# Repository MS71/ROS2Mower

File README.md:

# ROS2Mower
autonomous ROS2 lawn mower

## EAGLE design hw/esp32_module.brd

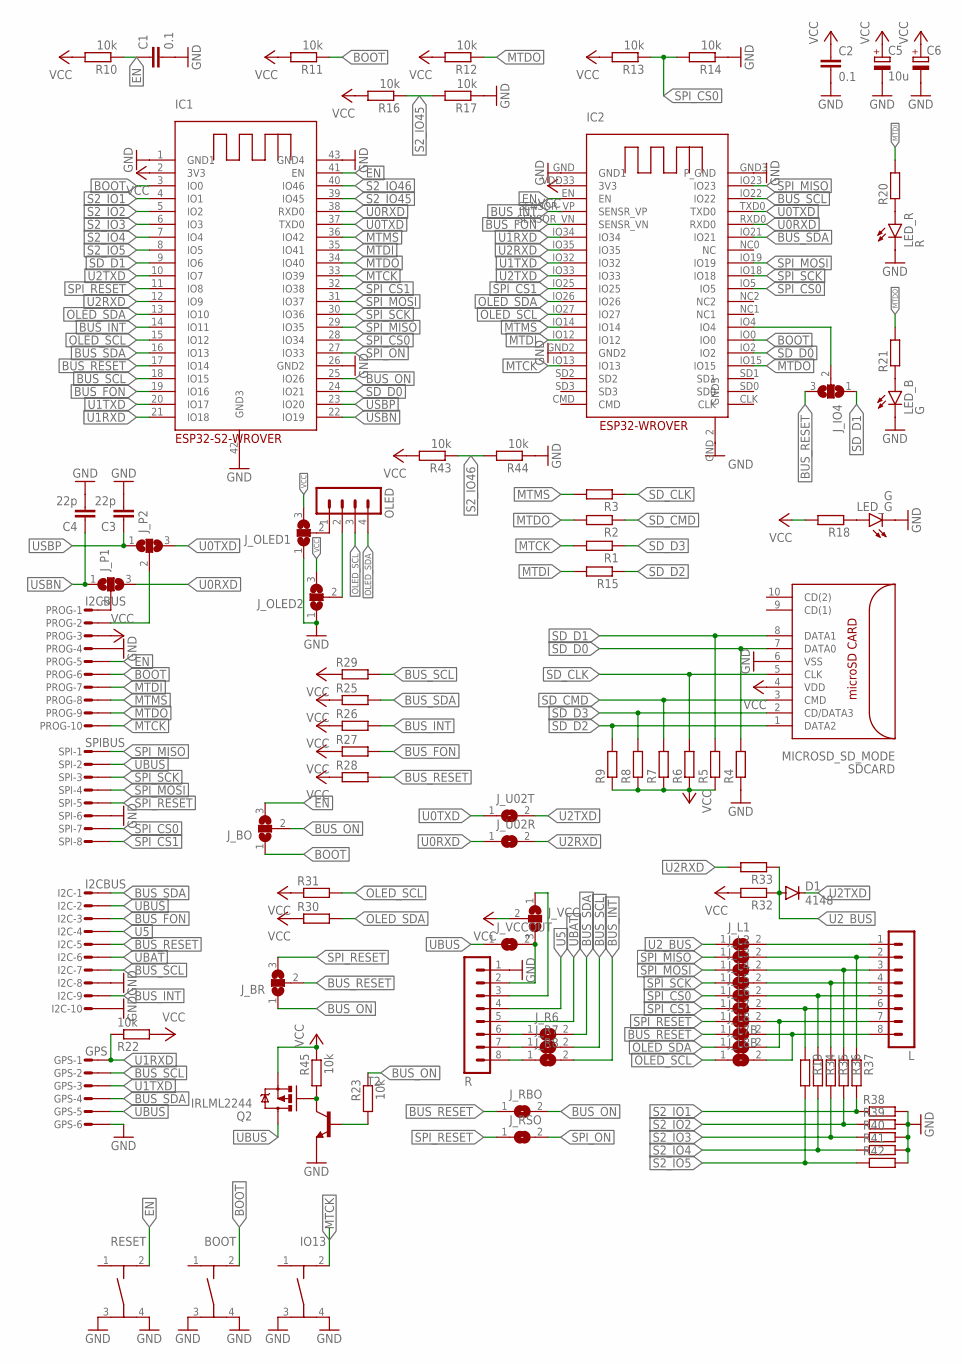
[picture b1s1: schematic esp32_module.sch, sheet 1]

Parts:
BOOT: TASTER-9314_SMD
C1, C2: 0.1; C0805
C3, C4: 22p; C0805
C5: 10u; B/3528-21W
C6: CPOL-EUC/6032-28R; C/6032-28R
D1: 4148; MINIMELF
GPS: GPS; MICROMATCH-6SMD
I2C: I2CBUS; MICROMATCH-10SMD
IC1: ESP32-S2_WROVER; ESP32-S2-WROVER
IC2: ESP32-WROVER
IO13: TASTER-9314_SMD
J_BO: SJ2W; SJ_2
J_BR: SJ2W; SJ_2
J_IO4: SJ2W; SJ_2
J_L1, J_L2, J_L3, J_L4, J_L5, J_L6, J_L7, J_L7B, J_L8, J_L8B: SJ
J_OLED1, J_OLED2: SJ2W; SJ_2
J_P1, J_P2: SJ2W; SJ_2
J_R6, J_R7, J_R8: SJ
J_RBO: SJ
J_RSO: SJ
J_U02R, J_U02T: SJ
J_VCC: SJ2W; SJ_2
J_VCCOUT: SJ
L: MA08-1
LED_B: G; CHIPLED_0805
LED_G: G; CHIPLED_0805
LED_R: R; CHIPLED_0805
OLED: MA04-1
PROG: I2CBUS; MICROMATCH-10SMD
Q2: IRLML2244; SOT23-3
R: MA08-1
R1, R2, R3, R4, R5, R6, R7, R8, R9, R15, R19, R25, R26, R27, R28, R29, R30, R31, R32, R33, R34, R35, R36, R37, R38, R39, R40, R41, R42: R-EU_R0805; R0805
R10, R11, R12, R13, R14, R16, R17, R22, R23, R43, R44, R45: 10k; R0805
R18, R20, R21: R-EU_R0603; R0603
RESET: TASTER-9314_SMD
SDCARD: MICROSD_SD_MODE; MICRO_SD_CONNECTOR
SPI: SPIBUS; MICROMATCH-8-SMD
T2: BC817-16-NPN-SOT23-BEC; SOT23-BEC

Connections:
BOOT: BOOT.2, IC1.3 (IO0), IC2.IO0, J_BO.1, PROG.6, R11.1
BUS_FON: I2C.3, IC1.19 (IO16), IC2.SENSOR_VN (SENSR_VN), R27.2
BUS_INT: I2C.9, IC1.14 (IO11), IC2.SENSOR_VP (SENSR_VP), J_R8.2, R26.2
BUS_ON: IC1.25 (IO26), J_BO.2, J_BR.1, J_RBO.2, R23.1
BUS_RESET: I2C.5, IC1.17 (IO14), J_BR.2, J_IO4.3, J_L8.1, J_RBO.1, R28.2
BUS_SCL: GPS.2, I2C.7, IC1.18 (IO15), IC2.IO22, J_R7.2, R29.2
BUS_SDA: GPS.4, I2C.1, IC1.16 (IO13), IC2.IO21, J_R6.2, R25.2
EN: C1.1, IC1.41 (EN), IC2.EN, J_BO.3, PROG.5, R10.1, RESET.2
GND: BOOT.3, BOOT.4, C1.2, C2.2, C3.2, C4.2, C5.-, C6.-, GPS.6, I2C.8, I2C.10, IC1.1 (GND1), IC1.26 (GND2), IC1.42 (GND3), IC1.43 (GND4), IC2.GND (GND1), IC2.GND2, IC2.GND3 (P_GND), IC2.GND_2 (GND3), IO13.3, IO13.4, J_OLED1.1, J_OLED2.1, LED_B.C, LED_G.C, LED_R.C, PROG.4, R.1, R4.1, R14.1, R17.1, R38.2, R39.2, R40.2, R41.2, R42.2, R44.1, RESET.3, RESET.4, SDCARD.6 (VSS), SPI.6, T2.E
LCD_1: J_OLED1.2, OLED.1
LCD_2: J_OLED2.2, OLED.2
MTCK: IC1.33 (IO39), IC2.IO13, IO13.2, PROG.10, R1.2
MTDI: IC1.35 (IO41), IC2.IO12, PROG.7, R15.2, R20.2
MTDO: IC1.34 (IO40), IC2.IO15, PROG.9, R2.2, R12.1, R21.2
MTMS: IC1.36 (IO42), IC2.IO14, PROG.8, R3.2
unnamed: IC2.IO4, J_IO4.2
unnamed: Q2.1 (G), R45.2, T2.C
unnamed: J_R6.1, R.6
unnamed: LED_G.A, R18.1
unnamed: J_R7.1, R.7
unnamed: J_P1.2, PROG.1
unnamed: J_R8.1, R.8
unnamed: R23.2, T2.B
unnamed: LED_R.A, R20.1
unnamed: LED_B.A, R21.1
unnamed: J_L7.2, J_L7B.2, L.7
unnamed: J_L6.2, L.6, R19.1
unnamed: J_L8.2, J_L8B.2, L.8
unnamed: J_L5.2, L.5, R34.1
unnamed: J_L4.2, L.4, R35.1
unnamed: J_L2.2, L.2, R37.1
unnamed: J_L3.2, L.3, R36.1
unnamed: J_L1.2, L.1
unnamed: J_P2.2, PROG.2
OLED_SCL: IC1.15 (IO12), IC2.IO27, J_L8B.1, OLED.3, R31.2
OLED_SDA: IC1.13 (IO10), IC2.IO26, J_L7B.1, OLED.4, R30.2
S2_IO1: IC1.4 (IO1), R37.2, R38.1
S2_IO2: IC1.5 (IO2), R36.2, R39.1
S2_IO3: IC1.6 (IO3), R35.2, R40.1
S2_IO4: IC1.7 (IO4), R34.2, R41.1
S2_IO5: IC1.8 (IO5), R19.2, R42.1
S2_IO45: IC1.39 (IO45), R16.1, R17.2
S2_IO46: IC1.40 (IO46), R43.1, R44.2
SD_CLK: R3.1, R6.2, SDCARD.5 (CLK)
SD_CMD: R2.1, R7.2, SDCARD.3 (CMD)
SD_D0: IC1.24 (IO21), IC2.IO2, R4.2, SDCARD.7 (DATA0)
SD_D1: IC1.9 (IO6), J_IO4.1, R5.2, SDCARD.8 (DATA1)
SD_D2: R9.2, R15.1, SDCARD.1 (DATA2)
SD_D3: R1.1, R8.2, SDCARD.2 (CD/DATA3)
SPI_CS0: IC1.28 (IO34), IC2.IO5, J_L5.1, R13.1, R14.2, SPI.7
SPI_CS1: IC1.32 (IO38), IC2.IO25, J_L6.1, SPI.8
SPI_MISO: IC1.29 (IO35), IC2.IO23, J_L2.1, SPI.1
SPI_MOSI: IC1.31 (IO37), IC2.IO19, J_L3.1, SPI.4
SPI_ON: IC1.27 (IO33), J_RSO.2
SPI_RESET: IC1.11 (IO8), J_BR.3, J_L7.1, J_RSO.1, SPI.5
SPI_SCK: IC1.30 (IO36), IC2.IO18, J_L4.1, SPI.3
U0RXD: IC1.38 (RXD0), IC2.RXD0, J_P1.3, J_U02R.1
U0TXD: IC1.37 (TXD0), IC2.TXD0, J_P2.3, J_U02T.1
U1RXD: GPS.1, IC1.21 (IO18), IC2.IO34, R22.1
U1TXD: GPS.3, IC1.20 (IO17), IC2.IO32
U2RXD: IC1.12 (IO9), IC2.IO35, J_U02R.2, R33.2
U2TXD: D1.C, IC1.10 (IO7), IC2.IO33, J_U02T.2
U2_BUS: D1.A, J_L1.1, R32.1, R33.1
U5: I2C.4, R.4
U33A: J_VCC.3, J_VCCOUT.2, R.2
U33B: J_VCC.1, R.3
UBAT: I2C.6, R.5
UBUS: GPS.5, I2C.2, J_VCCOUT.1, Q2.3 (D), SPI.2
USBN: C4.1, IC1.22 (IO19), J_P1.1
USBP: C3.1, IC1.23 (IO20), J_P2.1
VCC: C2.1, C5.+, C6.+, IC1.2 (3V3), IC2.VDD33 (3V3), J_OLED1.3, J_OLED2.3, J_VCC.2, PROG.3, Q2.2 (S), R5.1, R6.1, R7.1, R8.1, R9.1, R10.2, R11.2, R12.2, R13.2, R16.2, R18.2, R22.2, R25.1, R26.1, R27.1, R28.1, R29.1, R30.1, R31.1, R32.2, R43.2, R45.1, SDCARD.4 (VDD)

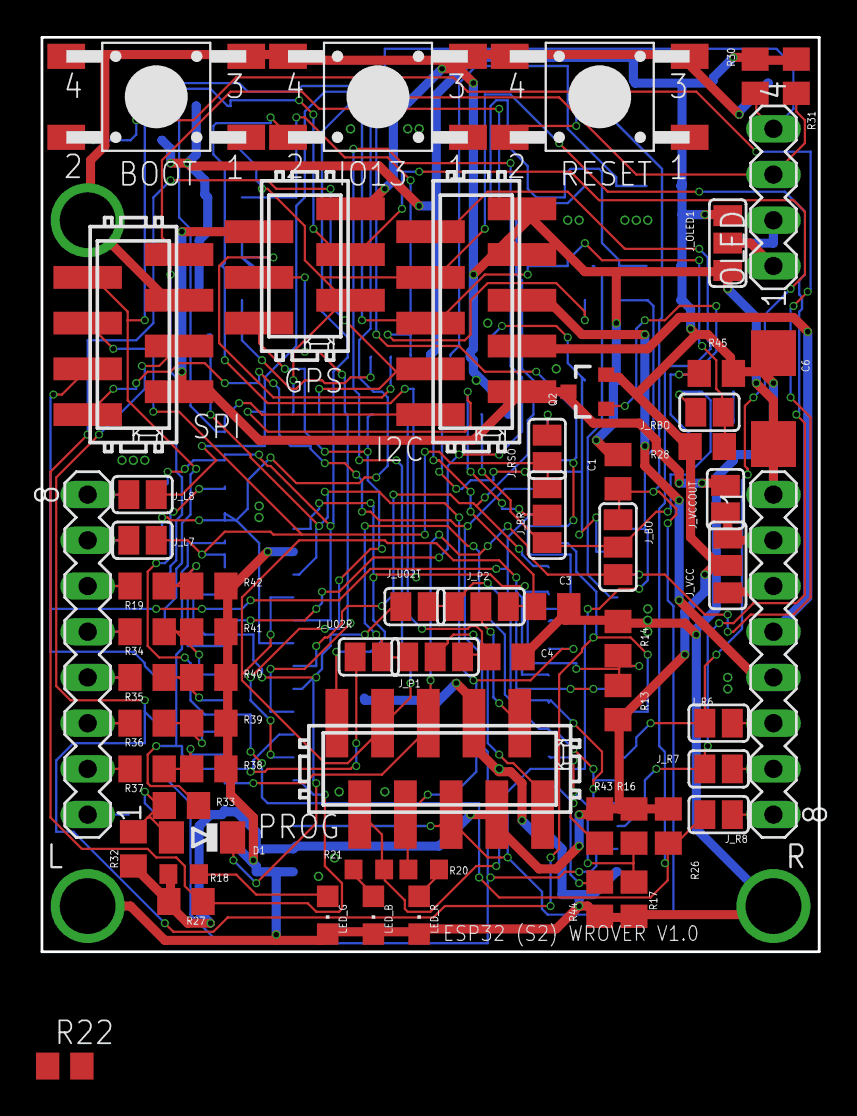
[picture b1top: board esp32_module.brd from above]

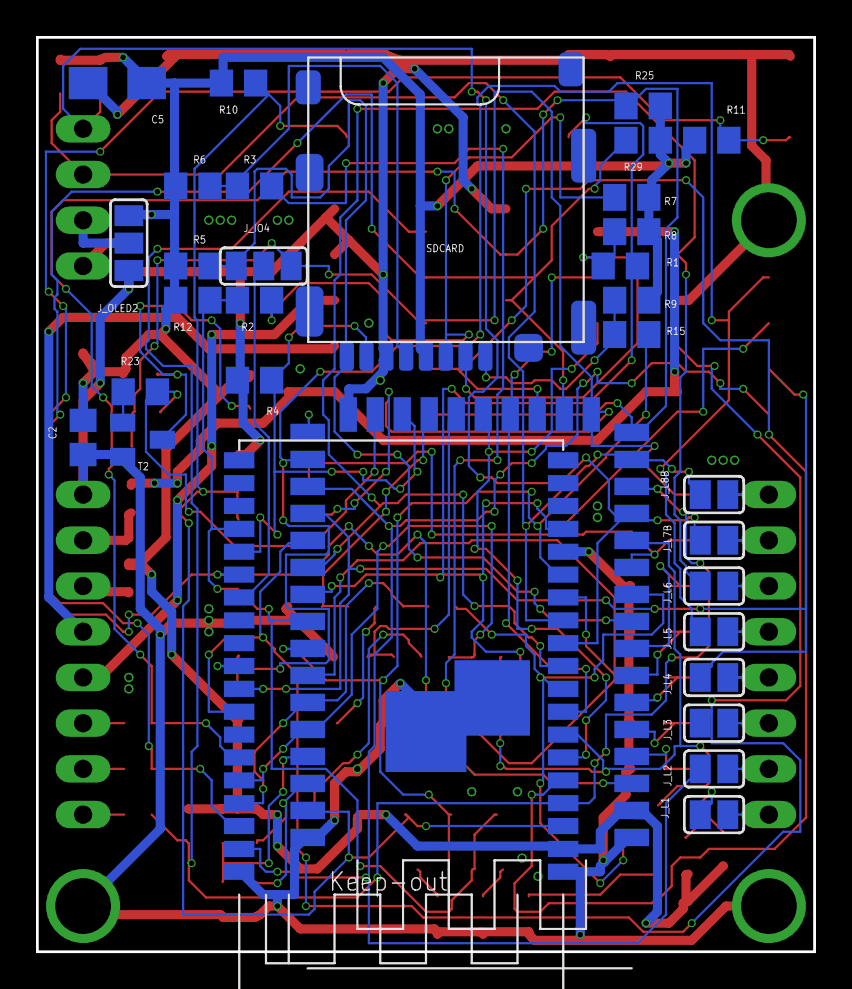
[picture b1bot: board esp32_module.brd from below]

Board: 2 copper layers, 43.2 x 50.8 mm, 95 parts (32 on the bottom side), 71 nets.

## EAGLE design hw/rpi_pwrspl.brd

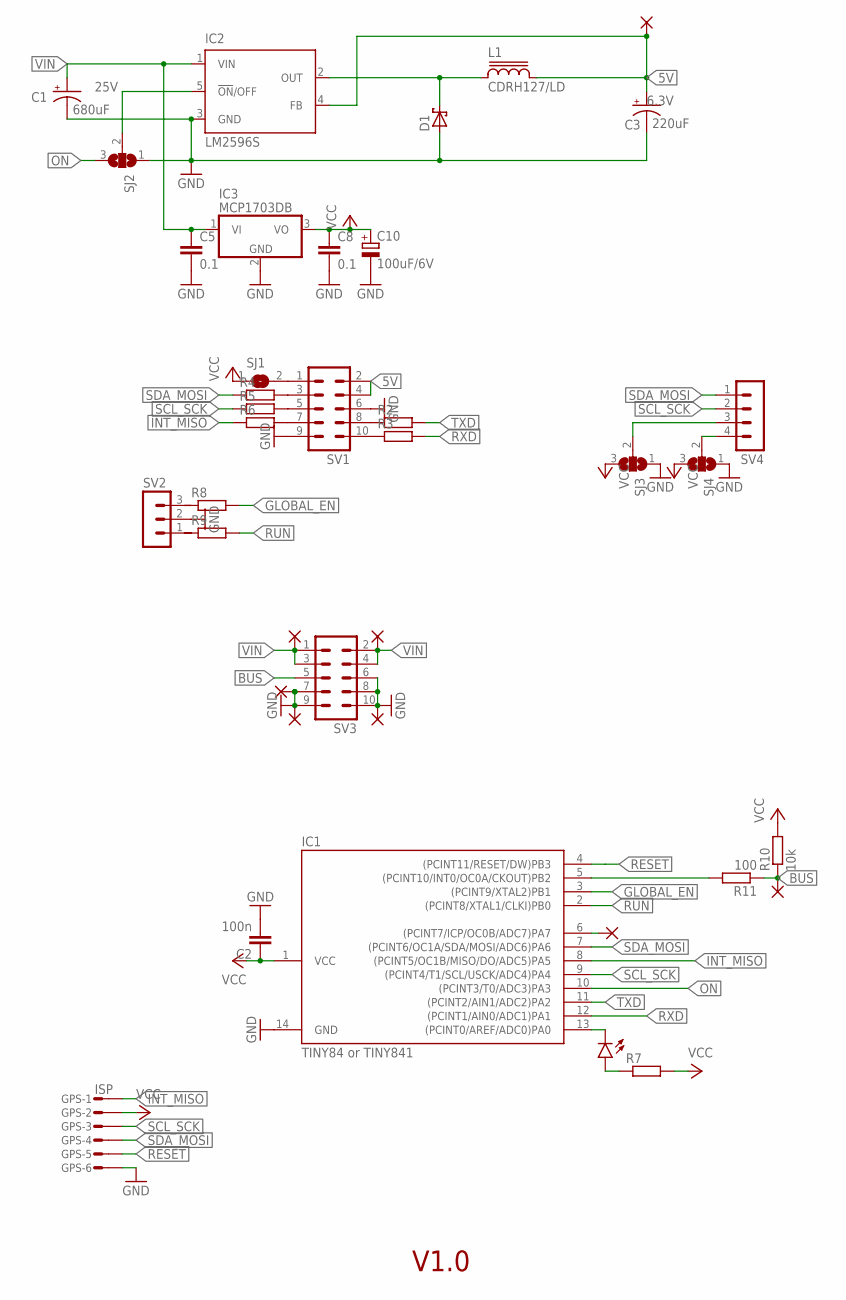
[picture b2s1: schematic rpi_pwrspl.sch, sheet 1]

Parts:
C1: 680uF; E5-10,5; VOLTAGE 25V
C2: 100n; C0805
C3: 220uF; UD-6,3X5,8_NICHICON; VOLTAGE 6.3V
C5, C8: 0.1; C0805
C10: 100uF/6V; B/3528-21R
D1: SCHOTTKY-DIODESMD; SMB
GPS: ISP; MICROMATCH-6SMD
IC1: TINY84 or TINY841; SOIC14
IC2: LM2596S; TO263-5
IC3: MCP1703DB; SOT223
L1: CDRH127/LD
LED: LEDCHIPLED_0805; CHIPLED_0805
PAD1, PAD2, PAD3, PAD6, PAD7: 1,6/0,9
PAD4, PAD5, PAD8: 2,54/1,1
R2, R3, R4, R5, R6, R8, R9: R-EU_M0805; M0805
R7: 100; R0603
R10: 10k; M0805
R11: 100; M0805
SJ1: SJ
SJ2, SJ3, SJ4: SJ2W; SJ_2
SV1, SV3: MA05-2
SV2: MA03-1
SV4: MA04-1

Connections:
5V: C3.+, IC2.4 (FB), L1.2, PAD6.1, SV1.2, SV1.4
BUS: PAD5.1, R10.1, R11.1, SV3.5
GLOBAL_EN: IC1.3 ((PCINT9/XTAL2)PB1), R8.2
GND: C1.-, C2.2, C3.-, C5.2, C8.2, C10.-, D1.A, GPS.6, IC1.14 (GND), IC2.3 (GND), IC3.2 (GND), PAD2.1, PAD3.1, PAD8.1, SJ2.1, SJ3.1, SJ4.1, SV1.6, SV1.9, SV2.2, SV3.6, SV3.7, SV3.8, SV3.9, SV3.10
INT_MISO: GPS.1, IC1.8 ((PCINT5/OC1B/MISO/DO/ADC5)PA5), R6.1
unnamed: SJ1.2, SV1.1
unnamed: R2.1, SV1.8
unnamed: R3.1, SV1.10
unnamed: R4.2, SV1.3
unnamed: LED.A, R7.1
unnamed: R5.2, SV1.5
unnamed: R6.2, SV1.7
unnamed: IC2.5 (!ON!/OFF), SJ2.2
unnamed: SJ4.2, SV4.4
unnamed: SJ3.2, SV4.3
unnamed: IC1.6 ((PCINT7/ICP/OC0B/ADC7)PA7), PAD7.1
unnamed: IC1.5 ((PCINT10/INT0/OC0A/CKOUT)PB2), R11.2
ON: IC1.10 ((PCINT3/T0/ADC3)PA3), SJ2.3
OUT: D1.C, IC2.2 (OUT), L1.1
PA0: IC1.13 ((PCINT0/AREF/ADC0)PA0), LED.C
RESET: GPS.5, IC1.4 ((PCINT11/RESET/DW)PB3)
RUN: IC1.2 ((PCINT8/XTAL1/CLKI)PB0), R9.2
RXD: IC1.12 ((PCINT1/AIN0/ADC1)PA1), R3.2
SCL_SCK: GPS.3, IC1.9 ((PCINT4/T1/SCL/USCK/ADC4)PA4), R5.1, SV4.2
SDA_MOSI: GPS.4, IC1.7 ((PCINT6/OC1A/SDA/MOSI/ADC6)PA6), R4.1, SV4.1
TXD: IC1.11 ((PCINT2/AIN1/ADC2)PA2), R2.2
VCC: C2.1, C8.1, C10.+, GPS.2, IC1.1 (VCC), IC3.3 (VO), R7.2, R10.2, SJ1.1, SJ3.3, SJ4.3
VIN: C1.+, C5.1, IC2.1 (VIN), IC3.1 (VI), PAD1.1, PAD4.1, SV3.1, SV3.2, SV3.3, SV3.4

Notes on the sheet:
V1.0

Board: 2 copper layers, 39 parts (5 on the bottom side), 28 nets, no tracks yet.

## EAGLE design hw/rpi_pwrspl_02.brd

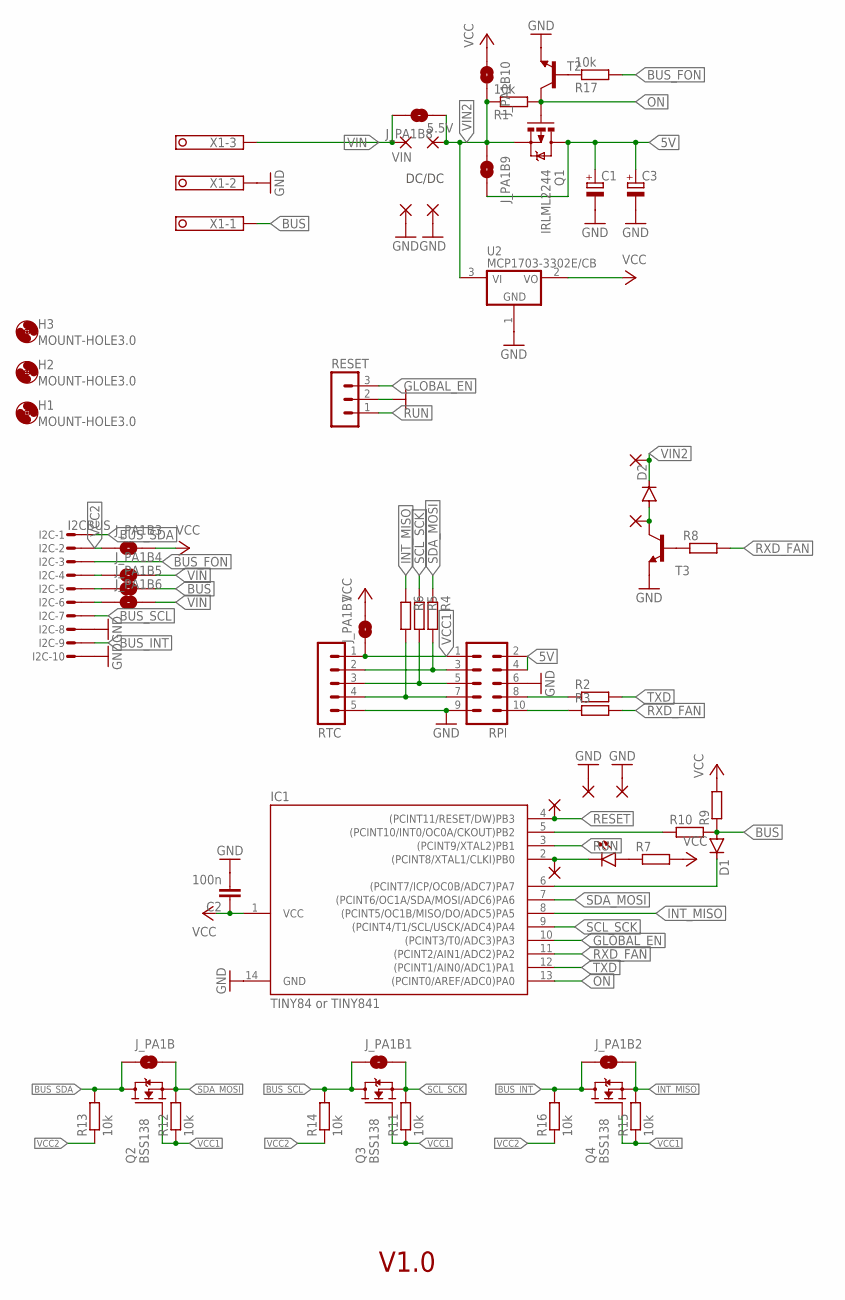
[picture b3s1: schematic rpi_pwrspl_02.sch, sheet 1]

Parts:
5.5V: 2,54/1,0
C1: CPOL-EUE5-5; E5-5
C2: 100n; C0805
C3: CPOL-EU085CS-1AR; 085CS_1AR
D1, D2: DIODE-MINIMELF; MINIMELF
DW, DW1, DW2, DW3, DW4, DW5: 1,6/0,9
H1, H2, H3: MOUNT-HOLE3.0; 3,0
I2C: I2CBUS; MICROMATCH-10SMD
IC1: TINY84 or TINY841; SOIC14
J_PA1B, J_PA1B1, J_PA1B2, J_PA1B3, J_PA1B4, J_PA1B5, J_PA1B6, J_PA1B7, J_PA1B8, J_PA1B9, J_PA1B10: JUMPER-SMT_2_NO_NO-SILK; SMT-JUMPER_2_NO_NO-SILK
LED: LEDCHIPLED_0805; CHIPLED_0805
PAD1, PAD2: 2,54/1,0
Q1: IRLML2244; SOT23-3
Q2, Q3, Q4: BSS138; SOT23
R1, R11, R12, R13, R14, R15, R16, R17: 10k; R0805
R2, R3, R4, R5, R6, R8, R9, R10: R-EU_M0805; M0805
R7: 100; R0603
RESET: MA03-1
RPI: MA05-2
RTC: MA05-1
T2, T3: BC817-16-NPN-SOT23-BEC; SOT23-BEC
U2: MCP1703-3302E/CB; SOT23A_MICROCHIP_CB
VIN: 2,54/1,0
X1: 1751251

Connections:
5V: C1.+, C3.+, J_PA1B9.2, Q1.3 (D), RPI.2, RPI.4
BUS: D1.A, J_PA1B5.2, R9.1, R10.2, X1.1
BUS_FON: I2C.3, R17.2
BUS_INT: I2C.9, J_PA1B2.1, Q4.3 (D), R16.2
BUS_SCL: I2C.7, J_PA1B1.1, Q3.3 (D), R14.2
BUS_SDA: I2C.1, J_PA1B.1, Q2.3 (D), R13.2
GLOBAL_EN: IC1.10 ((PCINT3/T0/ADC3)PA3), RESET.3
GND: C1.-, C2.2, C3.-, DW2.1, DW3.1, I2C.8, I2C.10, IC1.14 (GND), PAD1.1, PAD2.1, RESET.2, RPI.6, RPI.9, RTC.5, T2.E, T3.E, U2.1 (GND), X1.2
INT_MISO: IC1.8 ((PCINT5/OC1B/MISO/DO/ADC5)PA5), J_PA1B2.2, Q4.2 (S), R6.1, R15.2
unnamed: I2C.4, J_PA1B4.1
unnamed: R4.2, RPI.3, RTC.2
unnamed: R2.1, RPI.8
unnamed: R3.1, RPI.10
unnamed: R5.2, RPI.5, RTC.3
unnamed: LED.A, R7.1
unnamed: R6.2, RPI.7, RTC.4
unnamed: D2.A, DW4.1, T3.C
unnamed: IC1.5 ((PCINT10/INT0/OC0A/CKOUT)PB2), R10.1
unnamed: D1.C, IC1.6 ((PCINT7/ICP/OC0B/ADC7)PA7)
unnamed: DW1.1, IC1.2 ((PCINT8/XTAL1/CLKI)PB0), LED.C
unnamed: R8.1, T3.B
unnamed: R17.1, T2.B
unnamed: I2C.6, J_PA1B6.1
unnamed: I2C.5, J_PA1B5.1
ON: IC1.13 ((PCINT0/AREF/ADC0)PA0), Q1.1 (G), R1.2, T2.C
RESET: DW.1, IC1.4 ((PCINT11/RESET/DW)PB3)
RUN: IC1.3 ((PCINT9/XTAL2)PB1), RESET.1
RXD_FAN: IC1.11 ((PCINT2/AIN1/ADC2)PA2), R3.2, R8.2
SCL_SCK: IC1.9 ((PCINT4/T1/SCL/USCK/ADC4)PA4), J_PA1B1.2, Q3.2 (S), R5.1, R11.2
SDA_MOSI: IC1.7 ((PCINT6/OC1A/SDA/MOSI/ADC6)PA6), J_PA1B.2, Q2.2 (S), R4.1, R12.2
TXD: IC1.12 ((PCINT1/AIN0/ADC1)PA1), R2.2
VCC: C2.1, IC1.1 (VCC), J_PA1B3.2, J_PA1B7.2, J_PA1B10.1, R7.2, R9.2, U2.2 (VO)
VCC1: J_PA1B7.1, Q2.1 (G), Q3.1 (G), Q4.1 (G), R11.1, R12.1, R15.1, RPI.1, RTC.1
VCC2: I2C.2, J_PA1B3.1, R13.1, R14.1, R16.1
VIN: J_PA1B4.2, J_PA1B6.2, J_PA1B8.2, VIN.1, X1.3
VIN2: 5.5V.1, D2.C, DW5.1, J_PA1B8.1, J_PA1B9.1, J_PA1B10.2, Q1.2 (S), R1.1, U2.3 (VI)

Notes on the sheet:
V1.0
DC/DC

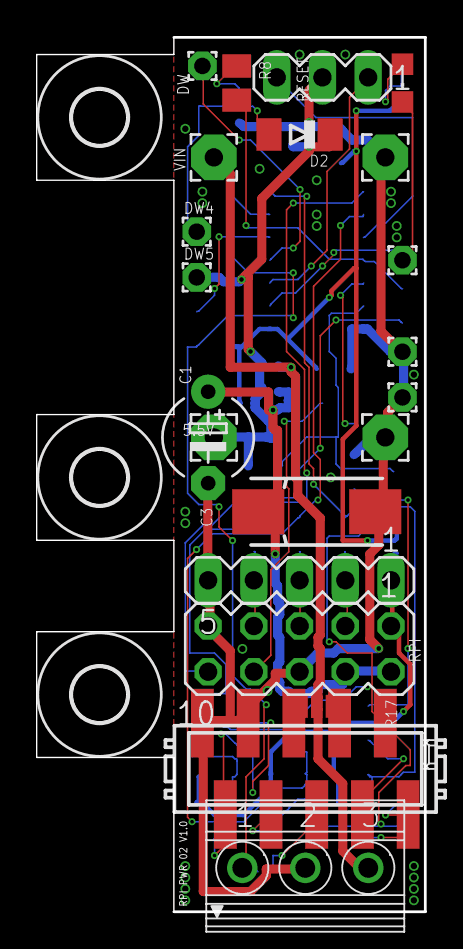
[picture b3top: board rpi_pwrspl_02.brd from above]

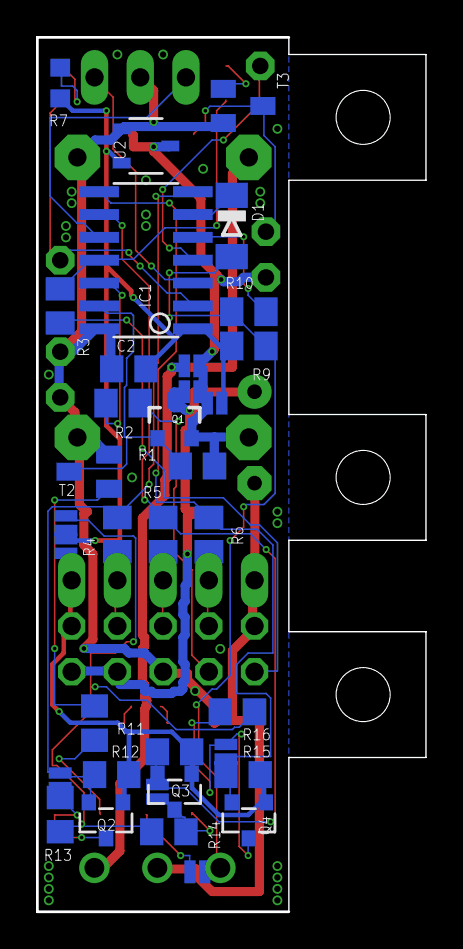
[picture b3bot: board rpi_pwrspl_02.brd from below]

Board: 2 copper layers, 21.6 x 48.6 mm, 60 parts (35 on the bottom side), 36 nets.

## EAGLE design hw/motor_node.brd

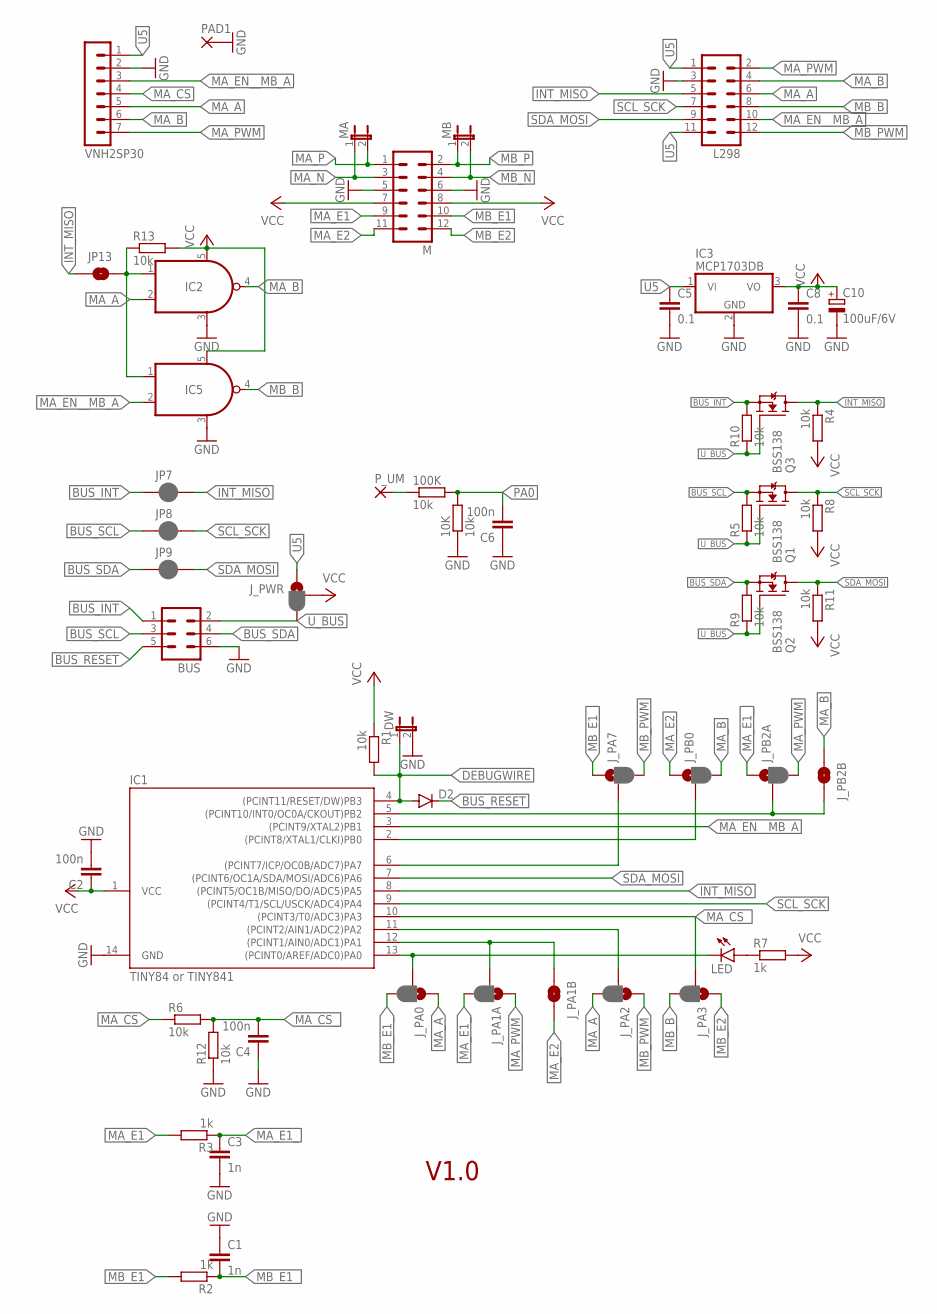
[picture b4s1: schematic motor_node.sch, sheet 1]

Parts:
10K, 100K: 10k; M0805
BUS: ML6
C1, C3: 1n; C0805
C2, C4, C6: 100n; C0805
C5, C8: 0.1; C0805
C10: 100uF/6V; B/3528-21R
D2: DIODE-MINIMELF; MINIMELF
DW: JP1E; JP1
IC1: TINY84 or TINY841; SOIC14
IC2, IC5: AHC00-DB; SOT-23/5
IC3: MCP1703DB; SOT223
JP7, JP8, JP9: JUMPER-SMT_2_NC_PASTE_NO-SILK; SMT-JUMPER_2_NC_PASTE_NO-SILK
JP13: JUMPER-SMT_2_NO_NO-SILK; SMT-JUMPER_2_NO_NO-SILK
J_PA0, J_PA1A, J_PA2, J_PA3, J_PA7: JUMPER-SMT_3_1-NC_PASTE_NO-SILK; SMT-JUMPER_3_1-NC_PASTE_NO-SILK
J_PA1B: JUMPER-SMT_2_NO_NO-SILK; SMT-JUMPER_2_NO_NO-SILK
J_PB0, J_PB2A: JUMPER-SMT_3_1-NC_PASTE_NO-SILK; SMT-JUMPER_3_1-NC_PASTE_NO-SILK
J_PB2B: JUMPER-SMT_2_NO_NO-SILK; SMT-JUMPER_2_NO_NO-SILK
J_PWR: JUMPER-SMT_3_1-NC_PASTE_NO-SILK; SMT-JUMPER_3_1-NC_PASTE_NO-SILK
L298: MA06-2
LED: LEDCHIPLED_0805; CHIPLED_0805
M: MA06-2
MA: JP1E; JP1
MB: JP1E; JP1
PAD1: 2,54/0,8
P_UM: 1,6/0,8
Q1, Q2, Q3: BSS138; SOT23
R1, R4, R6, R8, R11, R12: 10k; M0805
R2, R3: 1k; M0805
R5, R9, R10, R13: 10k; R0805
R7: 1k; R0603
VNH2SP30: MA07-1

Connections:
BUS_INT: BUS.1, JP7.1, Q3.2 (S), R10.2
BUS_RESET: BUS.5, D2.C
BUS_SCL: BUS.3, JP8.1, Q1.2 (S), R5.2
BUS_SDA: BUS.4, JP9.1, Q2.2 (S), R9.2
DEBUGWIRE: D2.A, DW.1, IC1.4 ((PCINT11/RESET/DW)PB3), R1.2
GND: 10K.1, BUS.6, C1.1, C2.2, C3.2, C4.1, C5.2, C6.1, C8.2, C10.-, DW.2, IC1.14 (GND), IC2.3 (GND), IC3.2 (GND), IC5.3 (GND), L298.3, M.5, M.6, PAD1.1, R12.1, VNH2SP30.2
INT_MISO: IC1.8 ((PCINT5/OC1B/MISO/DO/ADC5)PA5), JP7.2, JP13.1, L298.5, Q3.3 (D), R4.1
MA_A: IC2.2 (I1), J_PA0.1, J_PA2.3, L298.6, VNH2SP30.5
MA_B: IC2.4 (O), J_PB0.3, J_PB2B.1, L298.4, VNH2SP30.6
MA_CS: R6.1, VNH2SP30.4
MA_CS_: C4.2, IC1.10 ((PCINT3/T0/ADC3)PA3), J_PA3.2, R6.2, R12.2
MA_E1: M.9, R3.2
MA_E1_: C3.1, J_PA1A.3, J_PB2A.1, R3.1
MA_E2: J_PA1B.2, J_PB0.1, M.11
MA_EN__MB_A: IC1.3 ((PCINT9/XTAL2)PB1), IC5.2 (I1), L298.10, VNH2SP30.3
MA_N: M.3, MA.1
MA_P: M.1, MA.2
MA_PWM: J_PA1A.1, J_PB2A.3, L298.2, VNH2SP30.7
MB_B: IC5.4 (O), J_PA3.3, L298.8
MB_E1: M.10, R2.2
MB_E1_: C1.2, J_PA0.3, J_PA7.1, R2.1
MB_E2: J_PA3.1, M.12
MB_N: M.4, MB.2
MB_P: M.2, MB.1
MB_PWM: J_PA2.1, J_PA7.3, L298.12
unnamed: 100K.1, P_UM.1
unnamed: IC2.1 (I0), IC5.1 (I0), JP13.2, R13.1
unnamed: LED.A, R7.1
PA0: 10K.2, 100K.2, C6.2, IC1.13 ((PCINT0/AREF/ADC0)PA0), J_PA0.2, LED.C
PA1: IC1.12 ((PCINT1/AIN0/ADC1)PA1), J_PA1A.2, J_PA1B.1
PA2: IC1.11 ((PCINT2/AIN1/ADC2)PA2), J_PA2.2
PA7: IC1.6 ((PCINT7/ICP/OC0B/ADC7)PA7), J_PA7.2
PB0: IC1.2 ((PCINT8/XTAL1/CLKI)PB0), J_PB0.2
PB2: IC1.5 ((PCINT10/INT0/OC0A/CKOUT)PB2), J_PB2A.2, J_PB2B.2
SCL_SCK: IC1.9 ((PCINT4/T1/SCL/USCK/ADC4)PA4), JP8.2, L298.7, Q1.3 (D), R8.1
SDA_MOSI: IC1.7 ((PCINT6/OC1A/SDA/MOSI/ADC6)PA6), JP9.2, L298.9, Q2.3 (D), R11.1
U5: C5.1, IC3.1 (VI), J_PWR.1, L298.1, L298.11, VNH2SP30.1
U_BUS: BUS.2, J_PWR.3, Q1.1 (G), Q2.1 (G), Q3.1 (G), R5.1, R9.1, R10.1
VCC: C2.1, C8.1, C10.+, IC1.1 (VCC), IC2.5 (VDD), IC3.3 (VO), IC5.5 (VDD), J_PWR.2, M.7, M.8, R1.1, R4.2, R7.2, R8.2, R11.2, R13.2

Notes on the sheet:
V1.0

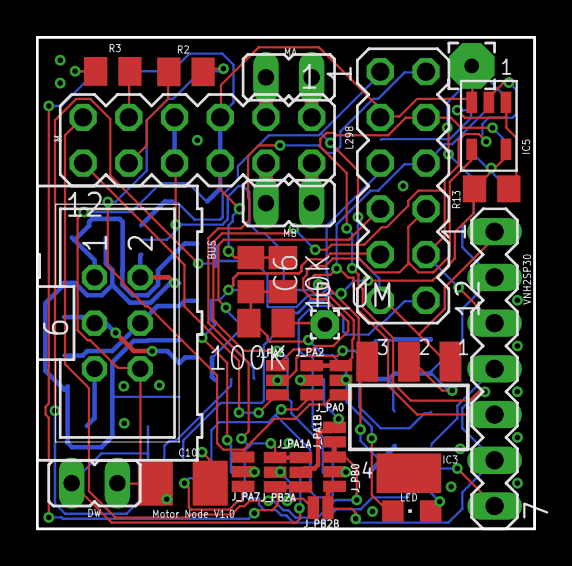
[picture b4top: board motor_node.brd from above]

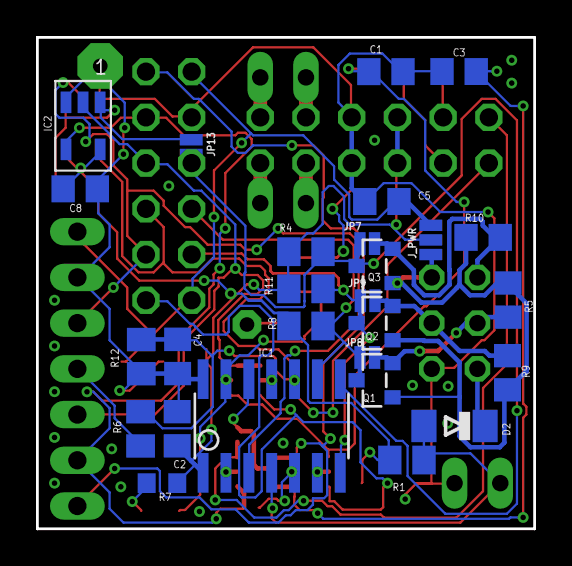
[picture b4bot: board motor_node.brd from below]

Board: 2 copper layers, 27.6 x 27.3 mm, 55 parts (27 on the bottom side), 39 nets.

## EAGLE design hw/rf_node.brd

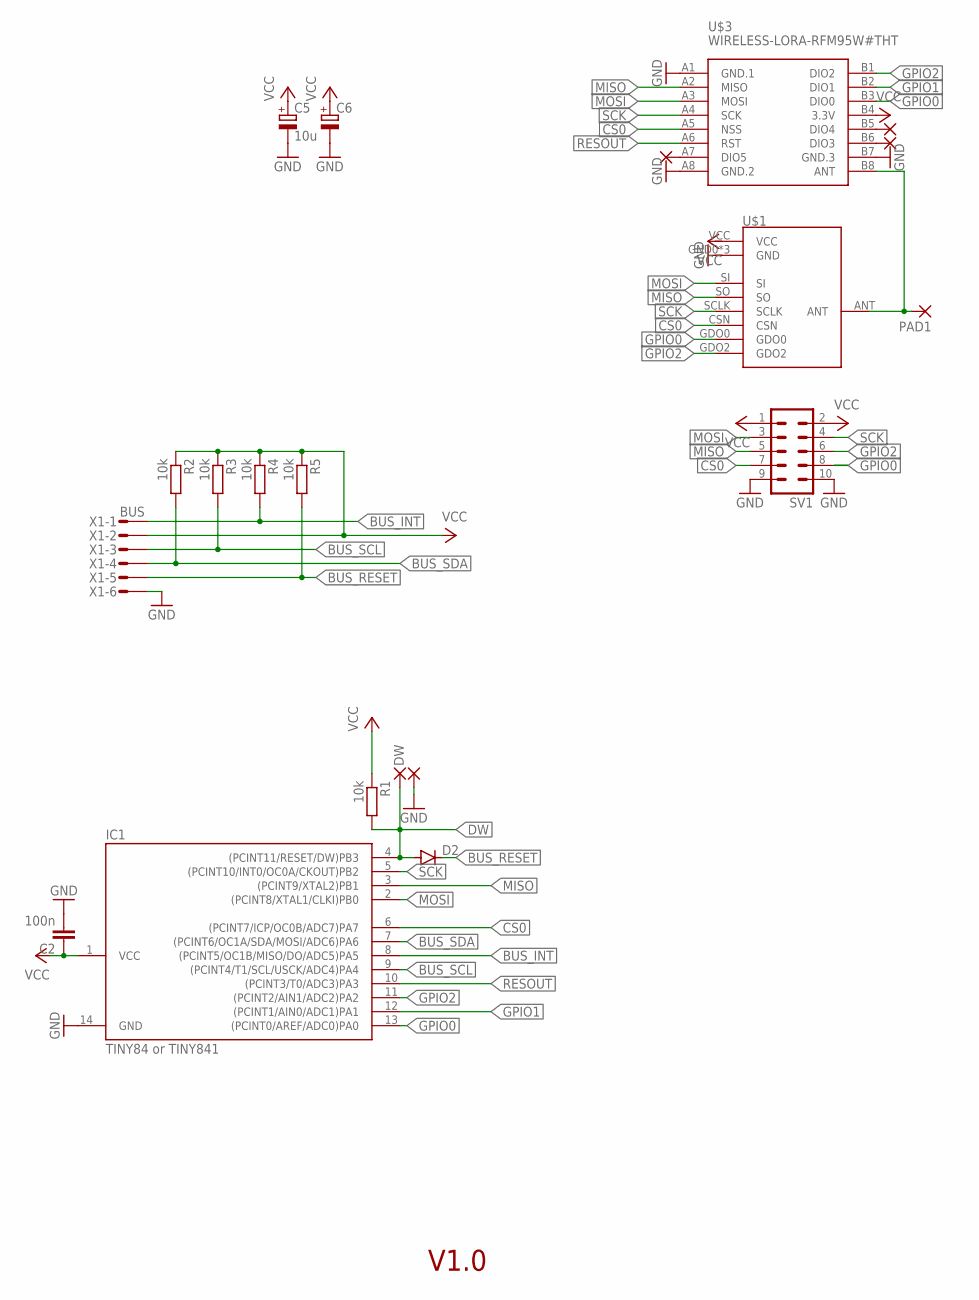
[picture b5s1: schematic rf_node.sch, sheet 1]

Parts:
C2: 100n; C0805
C5: 10u; B/3528-21W
C6: CPOL-EUC/6032-28R; C/6032-28R
D2: DIODE-MINIMELF; MINIMELF
DW: 1,6/0,9
GND_: 1,6/0,9
IC1: TINY84 or TINY841; SOIC14
PAD1, PAD2, PAD3, PAD4: 1,6/0,8
R1, R2, R3, R4, R5: 10k; M0805
SV1: MA05-2
U$1: CC1101
U$3: WIRELESS-LORA-RFM95W#THT
X1: BUS; MICROMATCH-6

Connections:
BUS_INT: IC1.8 ((PCINT5/OC1B/MISO/DO/ADC5)PA5), R4.2, X1.1
BUS_RESET: D2.C, R5.2, X1.5
BUS_SCL: IC1.9 ((PCINT4/T1/SCL/USCK/ADC4)PA4), R3.2, X1.3
BUS_SDA: IC1.7 ((PCINT6/OC1A/SDA/MOSI/ADC6)PA6), R2.2, X1.4
CS0: IC1.6 ((PCINT7/ICP/OC0B/ADC7)PA7), SV1.7, U$1.CSN, U$3.A5 (NSS)
DW: D2.A, DW.1, IC1.4 ((PCINT11/RESET/DW)PB3), R1.2
GND: C2.2, C5.-, C6.-, GND_.1, IC1.14 (GND), SV1.9, SV1.10, U$1.GND0 (GND), U$1.GND1 (GND), U$1.GND2 (GND), U$3.A1 (GND.1), U$3.A8 (GND.2), U$3.B7 (GND.3), X1.6
GPIO0: IC1.13 ((PCINT0/AREF/ADC0)PA0), SV1.8, U$1.GDO0, U$3.B3 (DIO0)
GPIO1: IC1.12 ((PCINT1/AIN0/ADC1)PA1), U$3.B2 (DIO1)
GPIO2: IC1.11 ((PCINT2/AIN1/ADC2)PA2), SV1.6, U$1.GDO2, U$3.B1 (DIO2)
MISO: IC1.3 ((PCINT9/XTAL2)PB1), SV1.5, U$1.SO, U$3.A2 (MISO)
MOSI: IC1.2 ((PCINT8/XTAL1/CLKI)PB0), SV1.3, U$1.SI, U$3.A3 (MOSI)
unnamed: PAD1.1, U$1.ANT, U$3.B8 (ANT)
unnamed: PAD2.1, U$3.B6 (DIO3)
unnamed: PAD3.1, U$3.B5 (DIO4)
unnamed: PAD4.1, U$3.A7 (DIO5)
RESOUT: IC1.10 ((PCINT3/T0/ADC3)PA3), U$3.A6 (RST)
SCK: IC1.5 ((PCINT10/INT0/OC0A/CKOUT)PB2), SV1.4, U$1.SCLK, U$3.A4 (SCK)
VCC: C2.1, C5.+, C6.+, IC1.1 (VCC), R1.1, R2.1, R3.1, R4.1, R5.1, SV1.1, SV1.2, U$1.VCC, U$3.B4 (3.3V), X1.2

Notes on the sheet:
V1.0

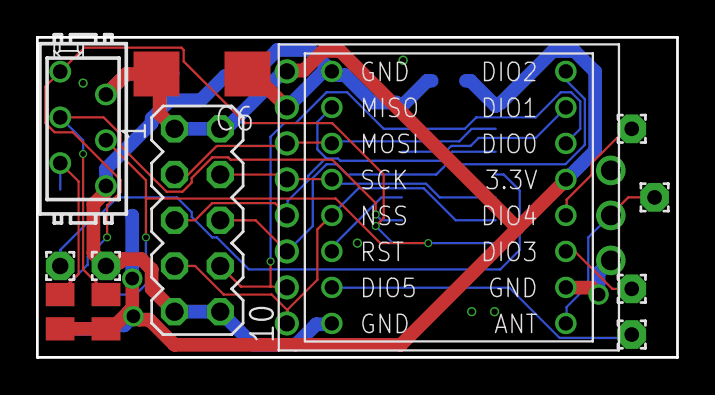
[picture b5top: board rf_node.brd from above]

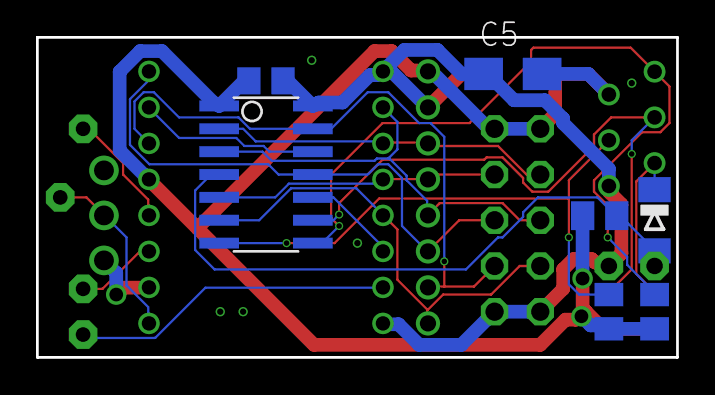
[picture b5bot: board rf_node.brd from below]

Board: 2 copper layers, 35.6 x 17.8 mm, 20 parts (7 on the bottom side), 19 nets.

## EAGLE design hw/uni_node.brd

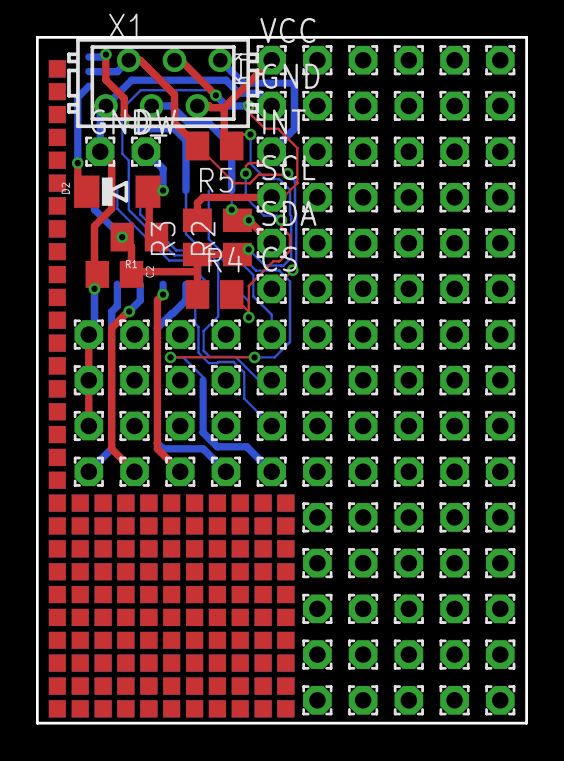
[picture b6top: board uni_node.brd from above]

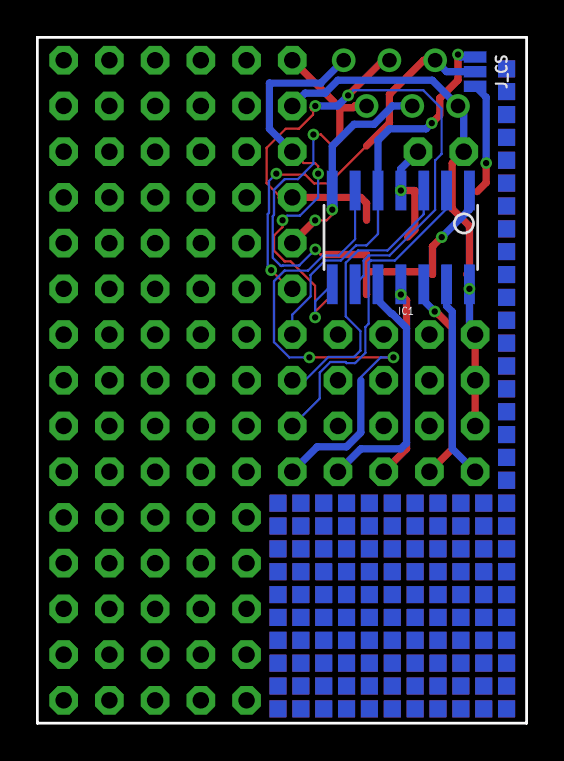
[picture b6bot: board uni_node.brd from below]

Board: 2 copper layers, 27.2 x 38.1 mm, 113 parts (2 on the bottom side), 16 nets.

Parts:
C2: 100n; C0805
CS: 1,6/0,9
D2: MINIMELF
DW: 1,6/0,9
GND: 1,6/0,9
GND_: 1,6/0,9
IC1: TINY84 or TINY841; SOIC14
INT, INT0: 1,6/0,9
J_CS: SMT-JUMPER_3_1-NC_PASTE_NO-SILK
PA0, PA1, PA2, PA3, PA7: 1,6/0,9
PAD1, PAD2, PAD3, PAD4, PAD5, PAD7, PAD8, PAD10, PAD11, PAD12, PAD13, PAD14, PAD15, PAD16, PAD18, PAD19, PAD20, PAD21, PAD22, PAD24, PAD25, PAD26, PAD28, PAD29, PAD30, PAD31, PAD33, PAD34, PAD35, PAD36, PAD37, PAD38, PAD39, PAD40, PAD43, PAD44, PAD45, PAD46, PAD47, PAD48, PAD49, PAD50, PAD51, PAD52, PAD53, PAD54, PAD55, PAD56, PAD57, PAD59, PAD60, PAD61, PAD62, PAD65, PAD66, PAD67, PAD68, PAD69, PAD70, PAD71, PAD72, PAD74, PAD75, PAD76, PAD78, PAD79, PAD80, PAD81, PAD82, PAD83, PAD84, PAD85, PAD86, PAD87, PAD89, PAD90, PAD91, PAD93, PAD94, PAD95, PAD96, PAD97, PAD98, PAD99, PAD100, PAD101, PAD102: 1,6/0,9
PB0, PB1: 1,6/0,9
R1, R2, R3, R4, R5: 10k; M0805
SCL: 1,6/0,9
SDA: 1,6/0,9
VCC: 1,6/0,9
X1: BUS; MICROMATCH-6

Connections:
BUS_INT: IC1.8, INT.1, R4.2, X1.1
BUS_P5: CS.1, J_CS.2, R5.2, X1.5
BUS_RESET: D2.C, J_CS.3
BUS_SCL: IC1.9, R3.2, SCL.1, X1.3
BUS_SDA: IC1.7, R2.2, SDA.1, X1.4
DW: D2.A, DW.1, IC1.4, R1.2
GND: C2.2, GND.1, GND_.1, IC1.14, PAD100.1, PAD101.1, PAD102.1, X1.6
INT0: IC1.5, INT0.1, J_CS.1
PA0: IC1.13, PA0.1
PA1: IC1.12, PA1.1
PA2: IC1.11, PA2.1
PA3: IC1.10, PA3.1
PA7: IC1.6, PA7.1
PB0: IC1.2, PB0.1
PB1: IC1.3, PB1.1
VCC: C2.1, IC1.1, R1.1, R2.1, R3.1, R4.1, R5.1, VCC.1, X1.2

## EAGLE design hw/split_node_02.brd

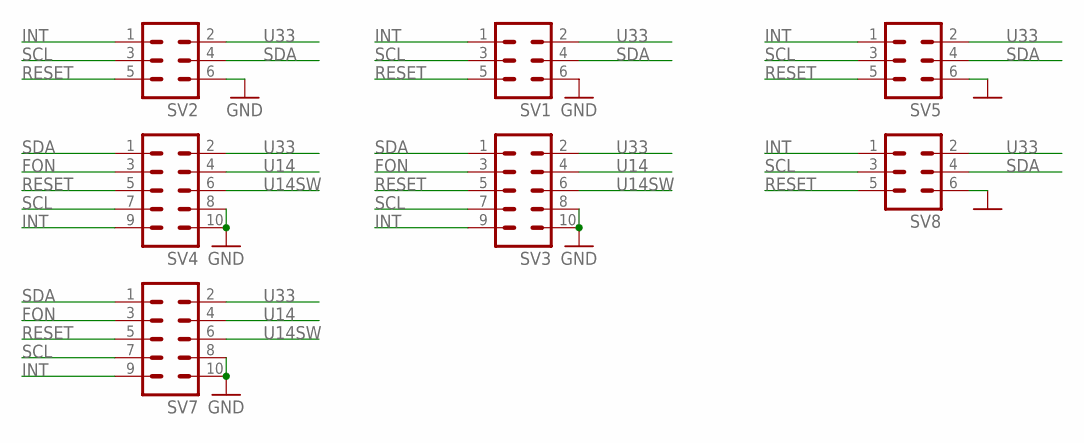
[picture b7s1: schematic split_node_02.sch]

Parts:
SV1, SV2, SV5, SV8: ML6
SV3, SV4, SV7: ML10

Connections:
FON: SV3.3, SV4.3, SV7.3
GND: SV1.6, SV2.6, SV3.8, SV3.10, SV4.8, SV4.10, SV5.6, SV7.8, SV7.10, SV8.6
INT: SV1.1, SV2.1, SV3.9, SV4.9, SV5.1, SV7.9, SV8.1
RESET: SV1.5, SV2.5, SV3.5, SV4.5, SV5.5, SV7.5, SV8.5
SCL: SV1.3, SV2.3, SV3.7, SV4.7, SV5.3, SV7.7, SV8.3
SDA: SV1.4, SV2.4, SV3.1, SV4.1, SV5.4, SV7.1, SV8.4
U14: SV3.4, SV4.4, SV7.4
U14SW: SV3.6, SV4.6, SV7.6
U33: SV1.2, SV2.2, SV3.2, SV4.2, SV5.2, SV7.2, SV8.2

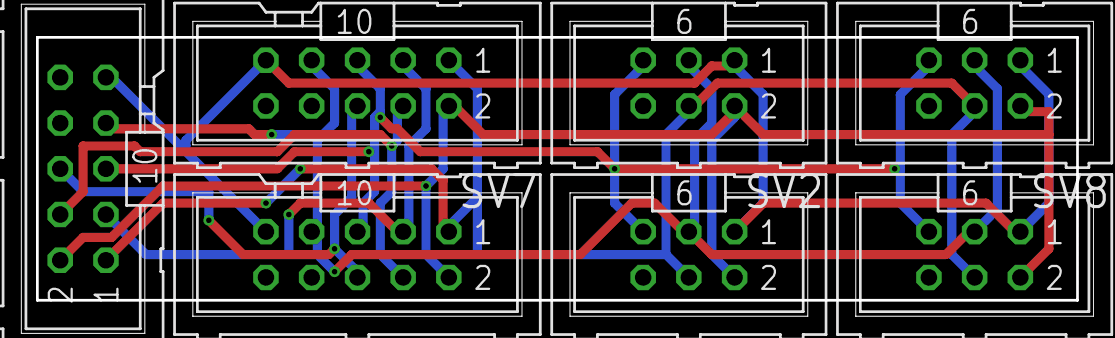
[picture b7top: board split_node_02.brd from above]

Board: 2 copper layers, 57.8 x 14.6 mm, 7 parts (0 on the bottom side), 9 nets.

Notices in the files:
parts and their libraries:
User-Submitted: Licensing: Creative Commons ShareAlike 4.0 International - https://creativecommons.org/licenses/by-sa/4.0
modules: Released under the Creative Commons Attribution 4.0 International License: http://creativecommons.org/licenses/by/4.0
inductor-sumida: Copyright (C) 2008, Bob Starr
